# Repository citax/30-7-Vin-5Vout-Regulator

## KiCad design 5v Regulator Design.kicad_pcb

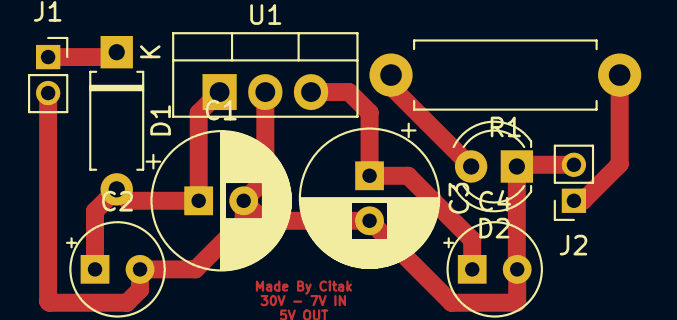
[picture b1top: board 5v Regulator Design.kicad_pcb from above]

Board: 2 copper layers, 10 parts (0 on the bottom side), 5 nets.

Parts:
C1: 0.22uF; CP_Radial_D7.5mm_P2.50mm
C2, C4: 0.1uF; CP_Radial_Tantal_D5.0mm_P2.50mm
C3: 10uF; CP_Radial_D7.5mm_P2.50mm
D1: DIODE; D_A-405_P7.62mm_Horizontal
D2: R_LED; LED_D4.0mm
J1, J2: 4P2C; PinSocket_1x02_P2.00mm_Vertical
R1: 330k; R_Axial_DIN0411_L9.9mm_D3.6mm_P12.70mm_Horizontal
U1: L7805; TO-220-3_Vertical

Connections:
unnamed: C1.1, C2.1, D1.2 (A), U1.1 (IN)
unnamed: C1.2, C2.2, C3.2, C4.2, D2.1 (K), J1.2, J2.2, U1.2 (GND)
unnamed: C3.1, C4.1, J2.1, R1.1, U1.3 (OUT)
unnamed: D1.1 (K), J1.1
unnamed: D2.2 (A), R1.2
